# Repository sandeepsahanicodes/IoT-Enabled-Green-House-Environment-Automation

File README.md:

# IoT Enabled Green House Environment Automation
- This is the research project for the partial fulfillment for the award of the degree of Bachelor of Technology in Computer Science and Engineering.
- Our system employs a network of sensors to gather data on essential greenhouse variables,
including temperature, humidity, soil moisture, and light intensity. We utilize the
ESP32 Wroom 32U microcontroller to transmit and visualize real-time data on the Arduino
Cloud platform. Once the data is stored, it undergoes comparison with optimal
values, triggering the operation of actuators accordingly. Historical data can be downloaded
from the Arduino Cloud in CSV format.

- As data transmission over the internet is susceptible to cyber attacks, our system incorporates
an attack detection layer. This layer identifies potential attacks on the network
and implements necessary measures to prevent breaches of confidential data.

- In our design, we have employed the ESP32 Wroom microcontroller for acquiring
sensor data, and the Arduino Cloud is utilized for storing the collected data. The DHT11
sensor is utilized for measuring humidity and temperature. For assessing soil water content,
a soil moisture sensor is utilized. An LDR module is employed for measuring light
intensity. Additionally, an LCD display is utilized for on-site monitoring of environmental
parameters.

## Our Contribution
- Automated Environment Control
- Remote Monitoring
- Network Attack Detection
- Notification System
  
## Hardware Used
- ESP32 Wroom Microcontroller
- DHT11 Module
- Mositure Sensor Module
- LDR Module
- I2C Liquid Crystal Display
- Relay Module
- Water Pump
- Cooling Fan
- Heating Lamp
- Power Supply
  
## Software Used
- Arduino Cloud
  
## Block Diagram

## Schematic Diagram

## Flow Chart

## Hardware Model

## Remote Monitoring Dashboard

## Project In Action
[Watch the full project explanation on YouTube](https://youtu.be/uN2EiPx5QiI)

## Authors
- [Subham Barik](https://www.linkedin.com/in/subham-b-a8b09027b/)
- [Sandeep Sahani](https://www.linkedin.com/in/sandeep-sahani-883398220/)
- [Satyabrat Sahoo](https://www.linkedin.com/in/satyabrat-sahoo-385aa6157/)
- [Manas Ranjan Kabat](https://www.linkedin.com/in/manas-ranjan-kabat-4b88933a/)

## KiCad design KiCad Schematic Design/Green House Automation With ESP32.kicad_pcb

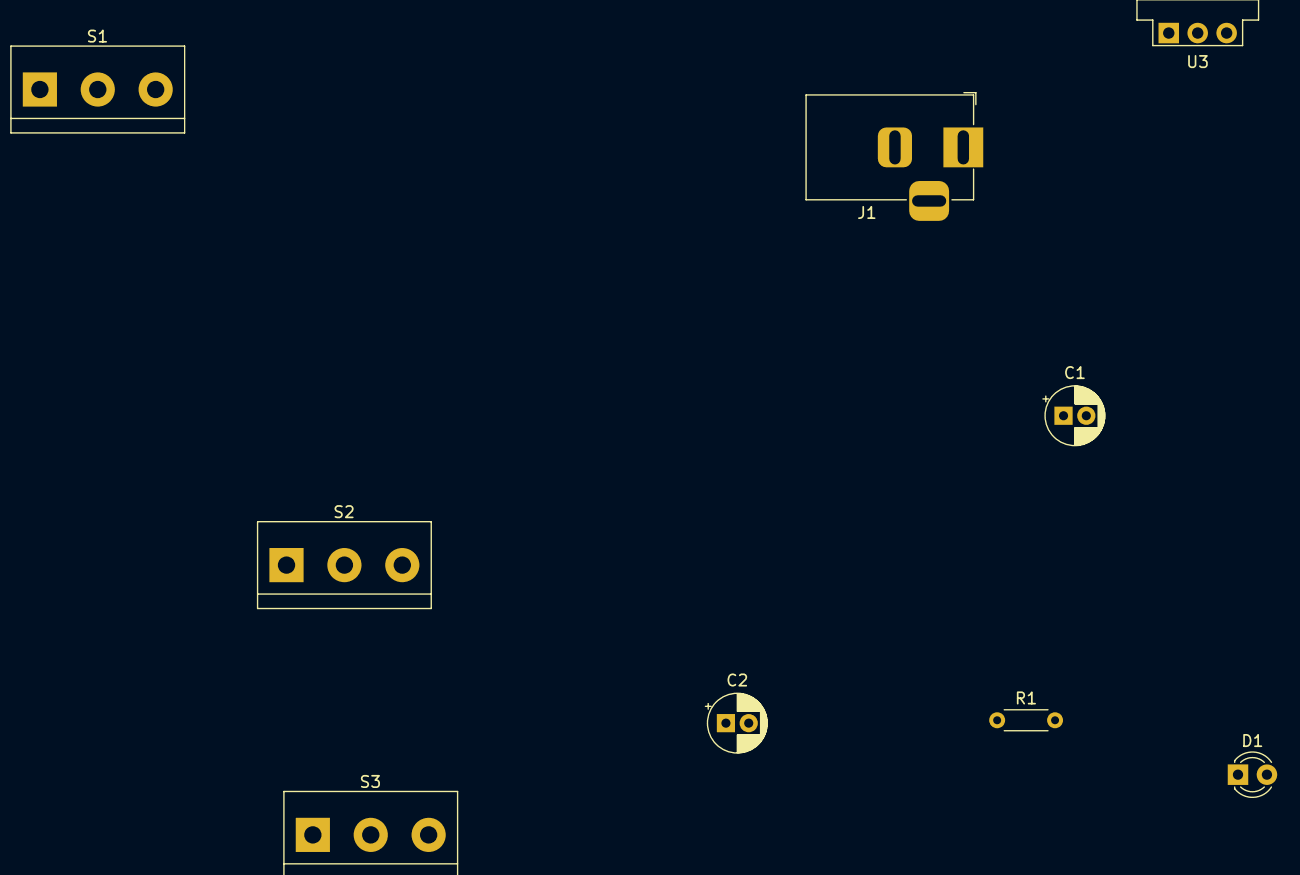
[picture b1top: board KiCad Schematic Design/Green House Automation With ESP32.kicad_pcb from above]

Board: 4 copper layers, 9 parts (0 on the bottom side), 4 nets, no tracks yet.

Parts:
C1, C2: 10u; CP_Radial_D5.0mm_P2.00mm
D1: LED; LED_D3.0mm
J1: 12V; BarrelJack_Horizontal
R1: 220R; R_Axial_DIN0204_L3.6mm_D1.6mm_P5.08mm_Horizontal
S1: DHT; TerminalBlock_bornier-3_P5.08mm
S2: Light; TerminalBlock_bornier-3_P5.08mm
S3: Moisture; TerminalBlock_bornier-3_P5.08mm
U3: L7805; Converter_DCDC_Murata_OKI-78SR_Vertical

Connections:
+5V: C1.1, D1.2 (A), S1.1, S2.1, U3.3 (OUT)
GND: C1.2, C2.2, J1.1, J1.2, R1.2, S1.3, S2.3, U3.2 (GND)
unnamed: D1.1 (K), R1.1
unnamed: C2.1, J1.3, U3.1 (IN)

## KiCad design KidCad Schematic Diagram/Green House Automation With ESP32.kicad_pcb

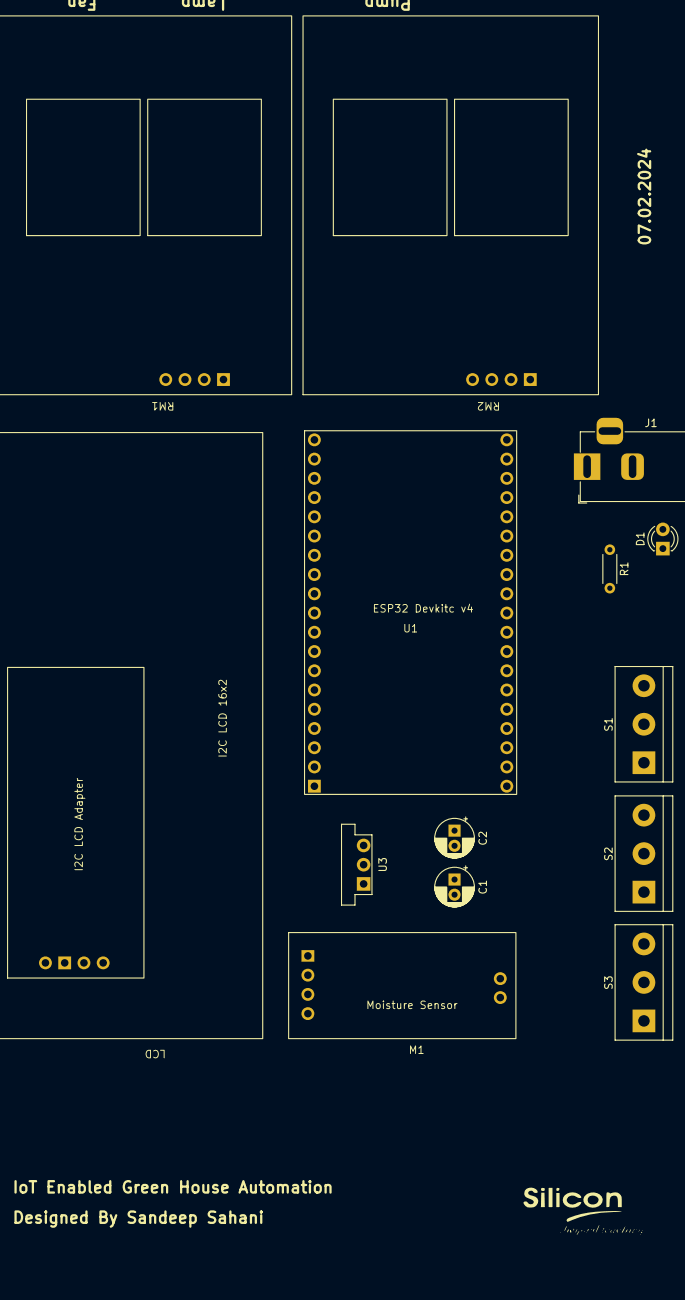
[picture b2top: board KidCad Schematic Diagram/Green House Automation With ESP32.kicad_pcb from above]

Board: 2 copper layers, 14 parts (0 on the bottom side), 14 nets, no tracks yet.

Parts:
C1, C2: 10u; CP_Radial_D5.0mm_P2.00mm
D1: LED; LED_D3.0mm
J1: 12V; BarrelJack_Horizontal
LCD: 12C_LCD_16X2
M1: Moisture Sensor
R1: 220R; R_Axial_DIN0204_L3.6mm_D1.6mm_P5.08mm_Horizontal
RM1, RM2: 2_Channel_Realy_Module
S1: DHT; TerminalBlock_bornier-3_P5.08mm
S2: Light; TerminalBlock_bornier-3_P5.08mm
S3: Moisture; TerminalBlock_bornier-3_P5.08mm
U1: ESP32 Devkitc v4
U3: L7805; Converter_DCDC_Murata_OKI-78SR_Vertical

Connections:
unnamed: C2.1, D1.2 (A), LCD.2 (VCC), M1.1 (VCC), RM1.4 (VCC), RM2.4 (VCC), S1.1, S2.1, U1.19 (5V), U3.3 (OUT)
unnamed: D1.1 (K), R1.1
unnamed: C1.2, C2.2, J1.1, J1.2, LCD.1 (GND), M1.2 (GND), R1.2, RM1.1 (GND), RM2.1 (GND), S1.3, S2.3, U1.32 (GND), U3.2 (GND)
unnamed: LCD.4 (SCL), U1.36 (GPIO22)
unnamed: LCD.3 (SDA), U1.33 (GPIO21)
unnamed: M1.4 (AO), U1.3 (VP)
unnamed: M1.5 (E1), S3.1
unnamed: M1.6 (E2), S3.2, S3.3
unnamed: RM1.2 (IN1), U1.9 (GPIO25)
unnamed: RM1.3 (IN2), U1.10 (GPIO26)
unnamed: RM2.2 (IN1), U1.11 (GPIO27)
unnamed: S1.2, U1.12 (GPIO14)
unnamed: S2.2, U1.4 (VN)
unnamed: C1.1, J1.3, U3.1 (IN)

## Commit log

2024-06-03 Add all files
2024-06-03 Remove ReadMe.adoc
2024-09-28 Added KiCad Schematic Diagram
2024-09-28 Removed wrong folder
2024-09-28 Added KiCad Schematic Design Folder
2024-09-28 Removed unwanted folders
